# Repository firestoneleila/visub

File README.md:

# visub
Code for a mini autonomous ROV project

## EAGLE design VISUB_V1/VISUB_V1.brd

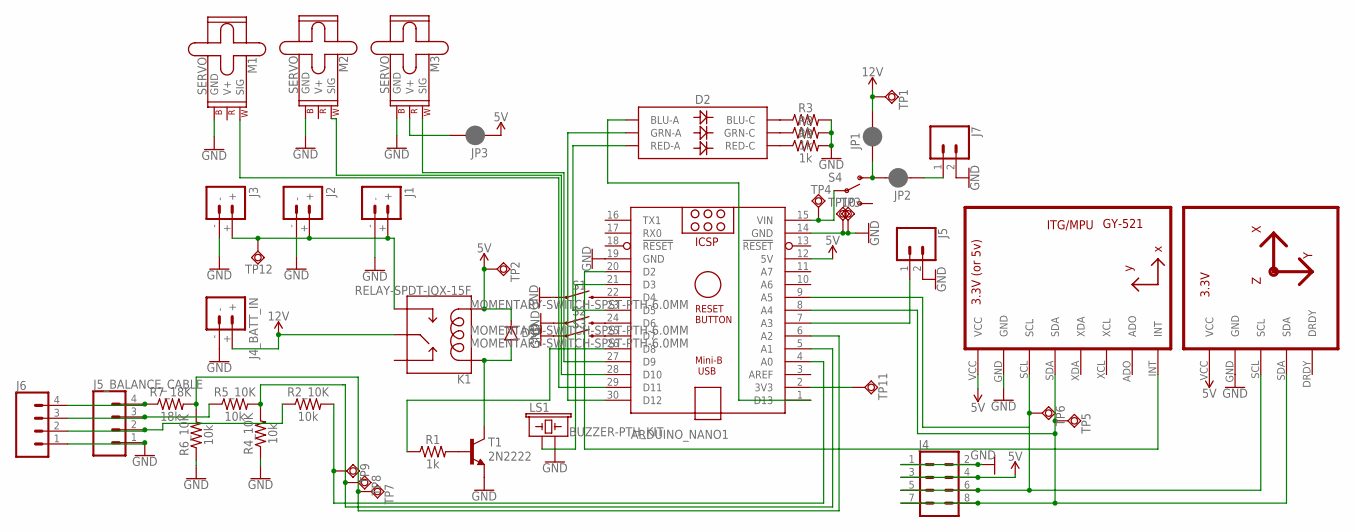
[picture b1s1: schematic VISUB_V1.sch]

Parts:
ARDUINO_NANO1: ARDUINO_NANO
D1: DIODE1N4148; DIODE-1N4148
D2: LED-RGBNO_IC; LED-TRICOLOR-5050
J1, J2, J3, J4_BATT_IN: BATTERY_CONN_DEANS; DEANS
J4: CONN_04X2; 2X4
J5, J7: CONN_02; 1X02
J5_BALANCE_CABLE, J6: CONN_04POLAR; MOLEX-1X4
JP1, JP2, JP3: JUMPER-SMT_2_NC_PASTE_SILK; SMT-JUMPER_2_NC_PASTE_SILK
K1: RELAY-SPDT-JQX-15F; RELAY-T90
LS1: BUZZER-PTH_KIT; BUZZER-12MM-KIT
M1, M2, M3: SERVO; 1X03
R1: 1k; AXIAL-0.3
R2_10K, R4_10K, R5_10K, R6_10K: 10k; AXIAL-0.3
R3, R8, R9: 1k; 0603
R7_18K: 18k; AXIAL-0.3
S1, S2, S3: MOMENTARY-SWITCH-SPST-PTH-6.0MM; TACTILE_SWITCH_PTH_6.0MM
S4: SWITCH-SPDT-PTH-11.6X4.0MM-LOCK; SWITCH_SPDT_PTH_11.6X4.0MM_LOCK
T1: 2N2222; TO92-EBC-OVAL
TP1, TP2, TP3, TP4, TP5, TP6, TP7, TP8, TP9, TP10, TP11, TP12: TESTPAD_TPSQB2,54; TESTPAD_B2,54
U1: GY-521MPU6050; GY-521
U2: HMC5883LGY-271; GY-271

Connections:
1S: ARDUINO_NANO1.4 (A0), R2_10K.P$2 (2), TP9.TP
2S: ARDUINO_NANO1.5 (A1), R4_10K.P$2 (2), R5_10K.P$2 (2), TP8.TP
3.3V: ARDUINO_NANO1.2 (3V3), TP11.TP
3S: ARDUINO_NANO1.6 (A2), R6_10K.P$2 (2), R7_18K.P$2 (2), TP7.TP
5V: ARDUINO_NANO1.12 (5V), D1.C, J4.3, J4.4, JP3.1, K1.COIL2, TP2.TP, U1.VCC, U2.VCC
12V: J4_BATT_IN.+, JP1.2, K1.MAIN, TP1.TP
BATT_OUT: J1.+, J2.+, J3.+, K1.NO, TP12.TP
D2: ARDUINO_NANO1.20 (D2), U1.INT
D3: ARDUINO_NANO1.21 (D3), LS1.+ (1)
D5: ARDUINO_NANO1.23 (D5), D2.2 (RED-A)
D8: ARDUINO_NANO1.26 (D8), R1.P$1 (1)
D9: ARDUINO_NANO1.27 (D9), M3.1 (SIG)
D10: ARDUINO_NANO1.28 (D10), M2.1 (SIG)
D11: ARDUINO_NANO1.29 (D11), M1.1 (SIG)
D12: ARDUINO_NANO1.30 (D12), D2.1 (GRN-A)
GND: ARDUINO_NANO1.14 (GND), ARDUINO_NANO1.19 (GND), J1.-, J2.-, J3.-, J4.1, J4.2, J4_BATT_IN.-, J5.2, J5_BALANCE_CABLE.1, J6.1, J7.2, LS1.- (2), M1.3 (GND), M2.3 (GND), M3.3 (GND), R3.2, R4_10K.P$1 (1), R6_10K.P$1 (1), R8.2, R9.2, S1.1, S2.1, S3.1, T1.E, TP3.TP, TP10.TP, U1.GND, U2.GND
unnamed: J7.1, JP2.1
unnamed: D1.A, K1.COIL1, T1.C
unnamed: R1.P$2 (2), T1.B
unnamed: JP3.2, M3.2 (V+)
unnamed: ARDUINO_NANO1.7 (A3), J5.1
unnamed: J5_BALANCE_CABLE.2, J6.2, R2_10K.P$1 (1)
unnamed: J5_BALANCE_CABLE.4, J6.4, R7_18K.P$1 (1)
unnamed: J5_BALANCE_CABLE.3, J6.3, R5_10K.P$1 (1)
unnamed: ARDUINO_NANO1.22 (D4), S1.3 (2)
unnamed: ARDUINO_NANO1.25 (D7), S3.3 (2)
unnamed: ARDUINO_NANO1.24 (D6), S2.3 (2)
unnamed: JP1.1, JP2.2, S4.1 (O)
unnamed: ARDUINO_NANO1.1 (D13), D2.3 (BLU-A)
unnamed: D2.4 (BLU-C), R3.1
unnamed: D2.6 (GRN-C), R8.1
unnamed: D2.5 (RED-C), R9.1
SCL: ARDUINO_NANO1.9 (A5), J4.5, J4.6, TP6.TP, U1.SCL, U2.SCL
SDA: ARDUINO_NANO1.8 (A4), J4.7, J4.8, TP5.TP, U1.SDA, U2.SDA
VIN: ARDUINO_NANO1.15 (VIN), S4.2, TP4.TP

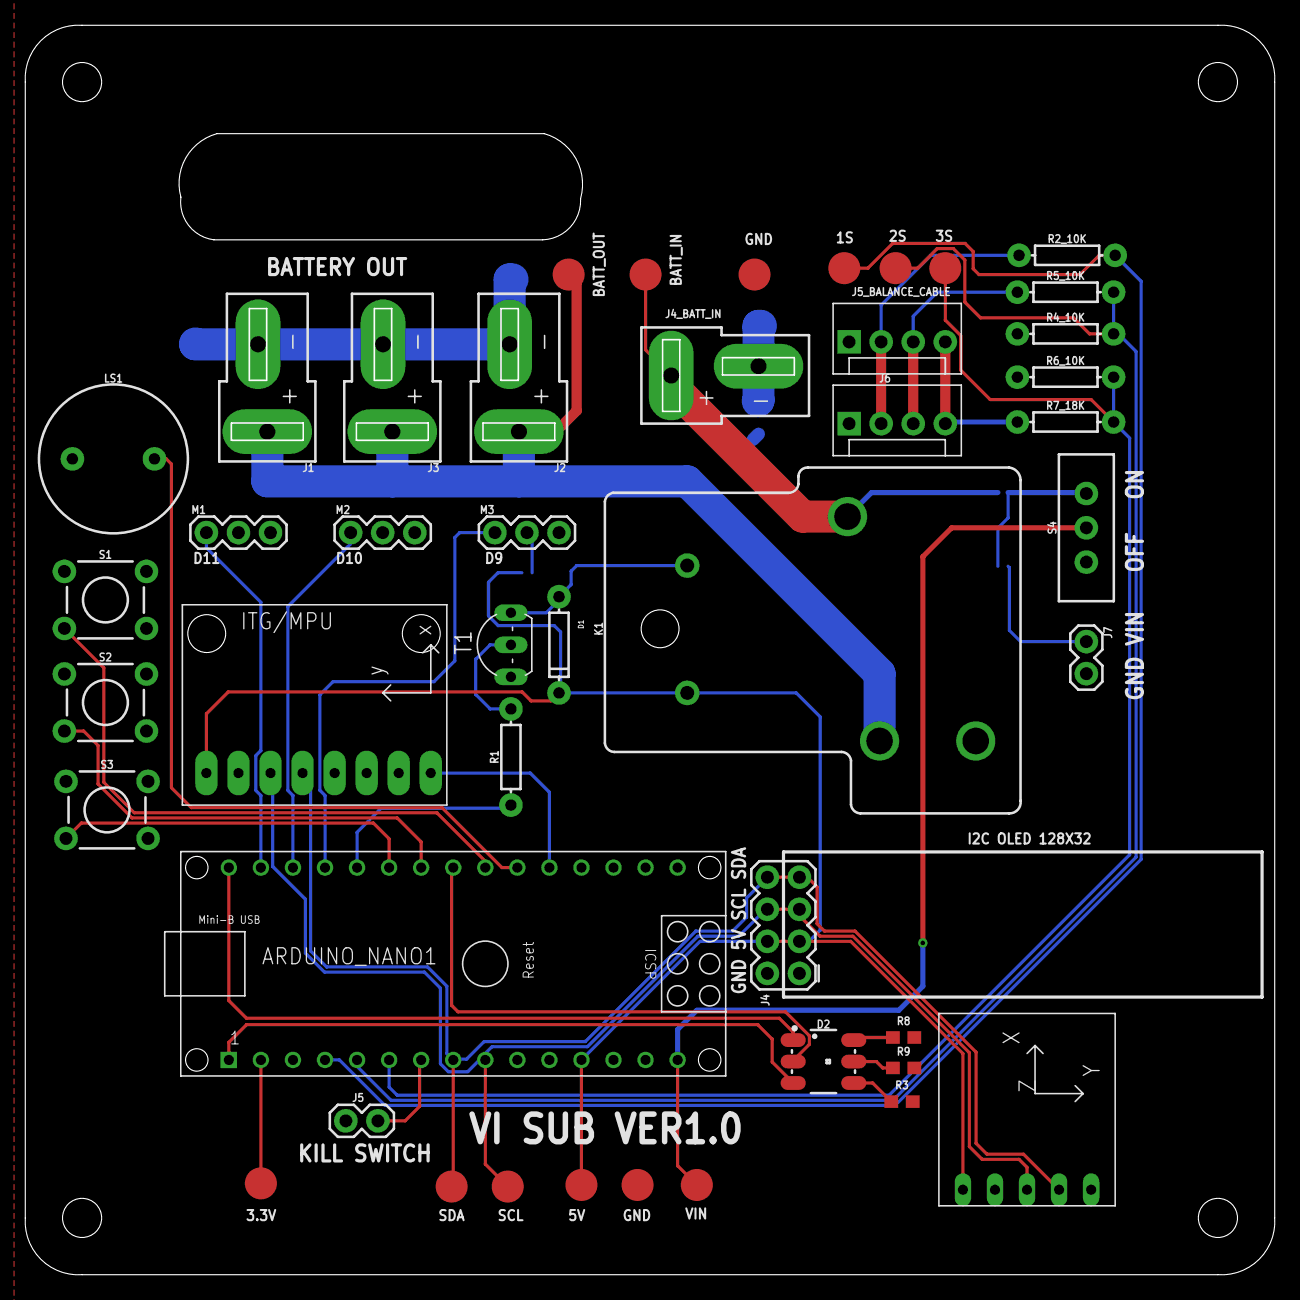
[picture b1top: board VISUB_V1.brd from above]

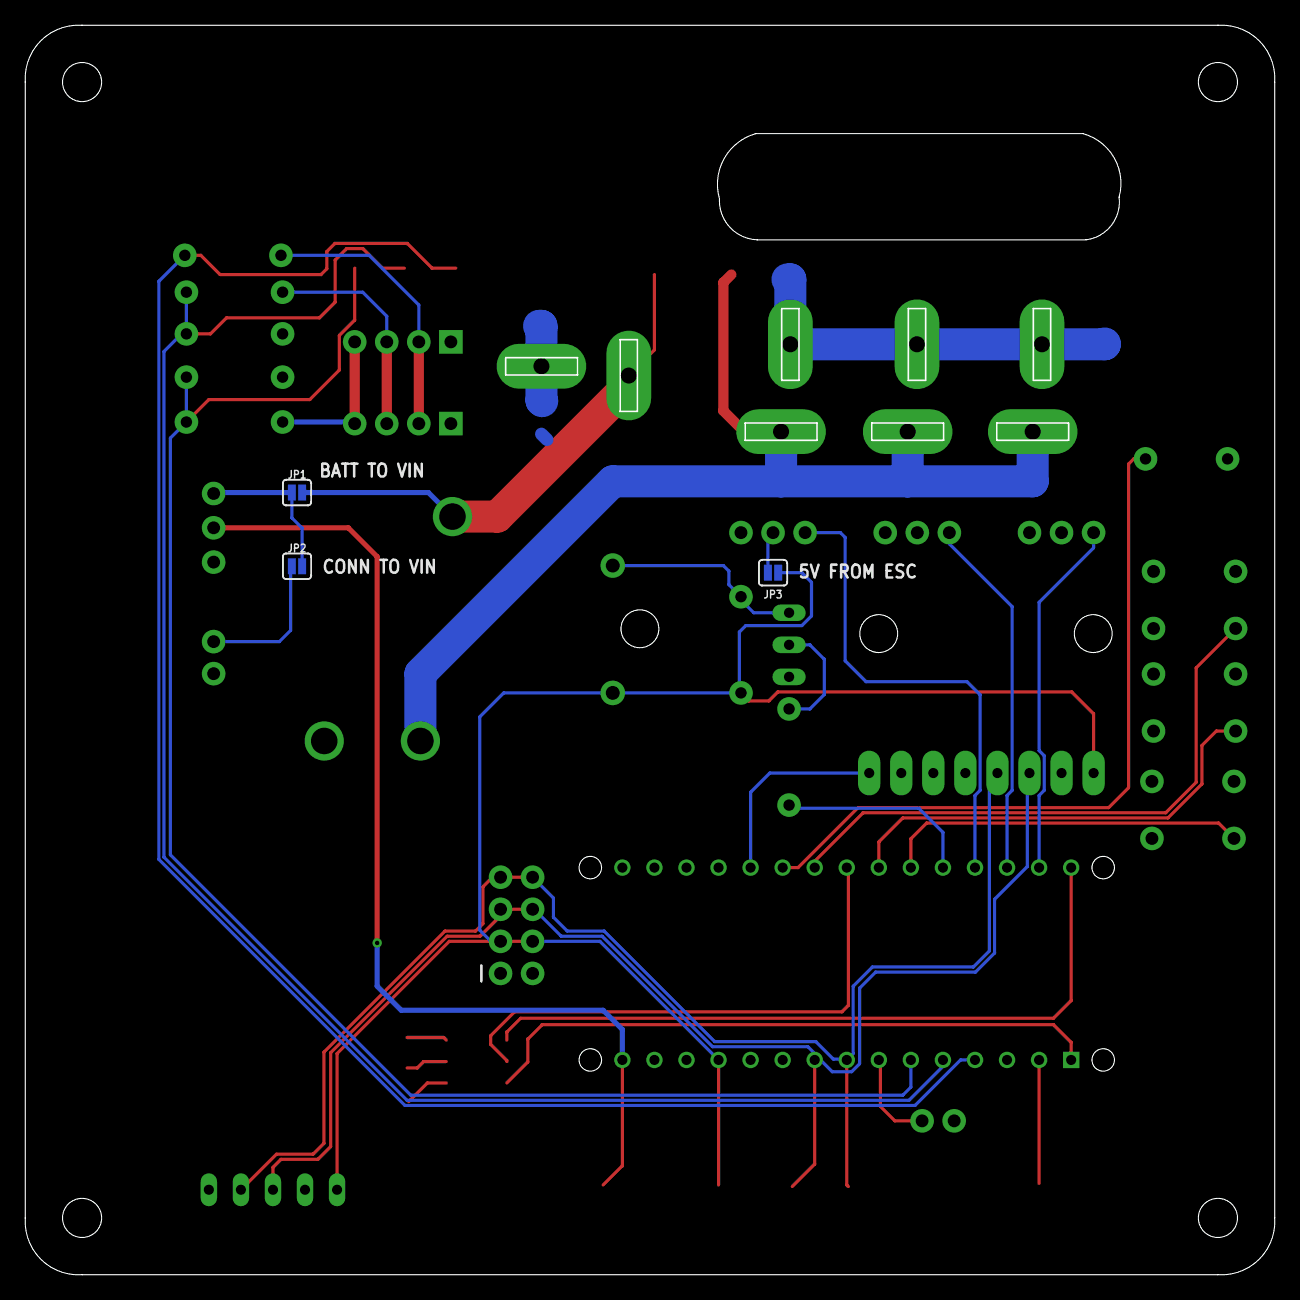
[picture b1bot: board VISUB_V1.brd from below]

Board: 2 copper layers, 98.9 x 98.9 mm, 48 parts (3 on the bottom side), 35 nets.

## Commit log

2019-09-14 Adding three motor test with v1 board
2019-09-15 Added PCB files for vi sub board v1
2020-03-03 added some imiages for the board

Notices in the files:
parts and their libraries:
SparkFun-Connectors: Licensing: Creative Commons ShareAlike 4.0 International - https://creativecommons.org/licenses/by-sa/4.0
